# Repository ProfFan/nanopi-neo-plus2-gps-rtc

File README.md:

# NanoPi GPS/RTC HAT

GPS Tested, RTC NOT Tested!

Note that you need to compile `GPSD` and `Chrony` yourself as the version supplied with Armbian DOES NOT WORK!

# BOM

| Id | Designator | Package                                         | Quantity | Designation       |
|----|------------|-------------------------------------------------|----------|-------------------|
| 1  | U2         | SOIC-16W_7.5x10.3mm_P1.27mm                     | 1        | DS3231M           |
| 2  | SW1        | SW_SPST_EVQPE1 淘宝贴片轻触开关，长方形的6mm长  | 1        | SW_Push           |
| 3  | R4,R3,R2   | R_0805_2012Metric                               | 3        | NP                |
| 4  | C2         | C_0805_2012Metric                               | 1        | 1u                |
| 5  | J4         | PinSocket_1x08_P2.54mm_Vertical 1P8 母头        | 1        | Conn_01x08_Female |
| 6  | J3         | PinSocket_1x12_P2.54mm_Vertical 1P12 母头       | 1        | Conn_01x12_Female |
| 7  | R1         | R_0805_2012Metric                               | 1        | 10                |
| 8  | L1         | L_0805_2012Metric                               | 1        | 27n               |
| 9  | J2         | PinHeader_2x12_P2.54mm_Vertical 2P12 母头       | 1        | NanoPi_GPIO       |
| 10 | C1         | C_0805_2012Metric                               | 1        | 47p               |
| 11 | BT1        | BatteryHolder_Seiko_MS621F 贴片纽扣电池 3V      | 1        | Battery_Cell      |
| 12 | J1         | U.FL_Molex_MCRF_73412-0110_Vertical 淘宝 uFL 座 | 1        | Conn_Coaxial      |
| 13 | U1         | KH-1110 立创，可买 JS-U810 （兼容）             | 1        | KH-1110-UB8X      |

# LICENSE

CERN OHL version 1.2

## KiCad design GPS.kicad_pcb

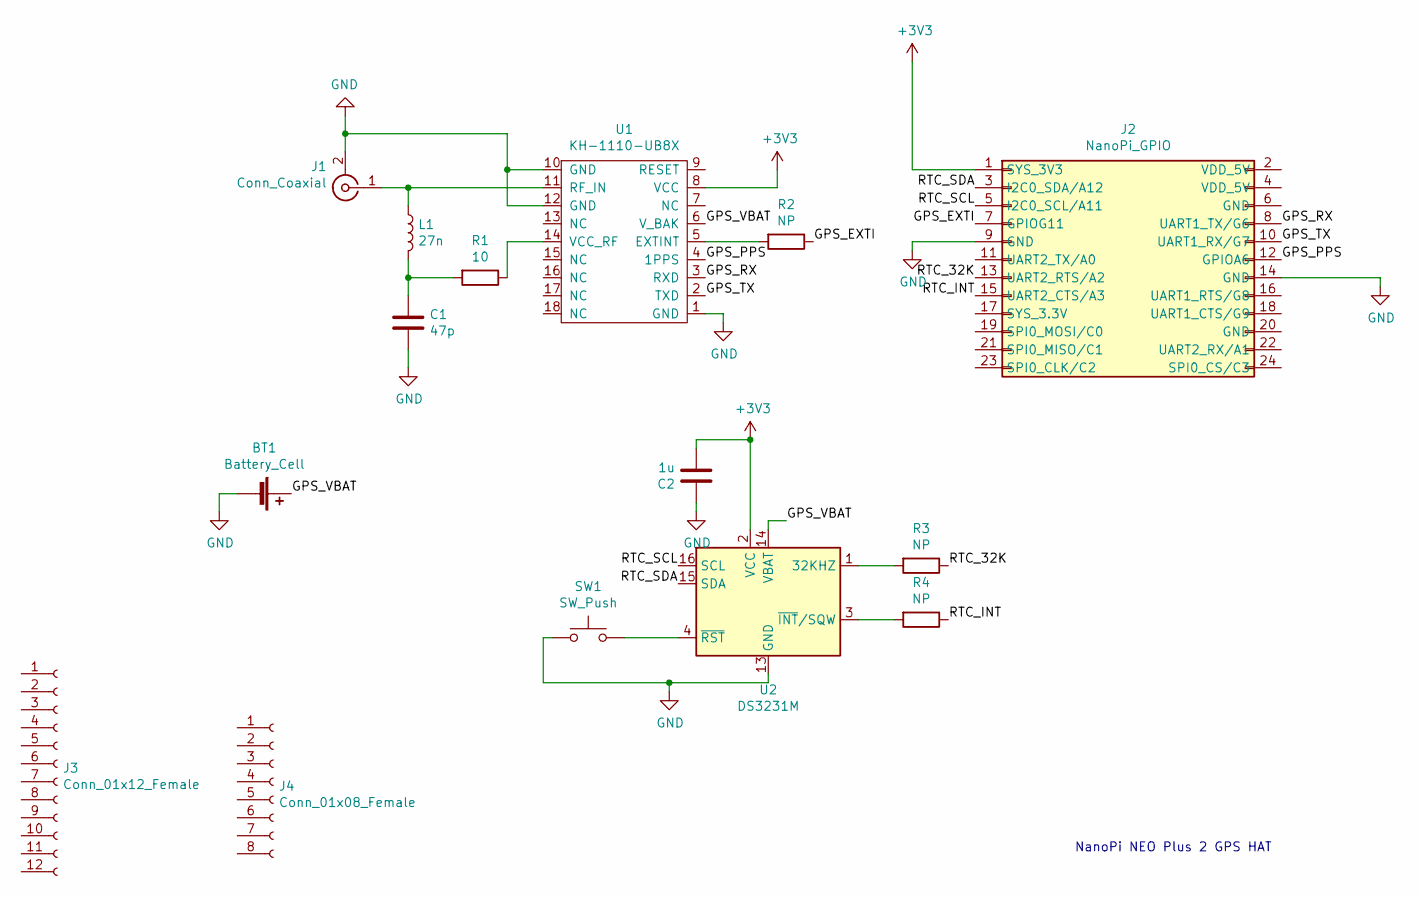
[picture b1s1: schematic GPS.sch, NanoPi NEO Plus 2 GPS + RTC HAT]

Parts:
BT1: Battery_Cell; BatteryHolder_Seiko_MS621F
C1: 47p; C_0805_2012Metric
C2: 1u; C_0805_2012Metric
J1: Conn_Coaxial; U.FL_Molex_MCRF_73412-0110_Vertical
J2: NanoPi_GPIO; PinHeader_2x12_P2.54mm_Vertical
J3: Conn_01x12_Female; PinSocket_1x12_P2.54mm_Vertical
J4: Conn_01x08_Female; PinSocket_1x08_P2.54mm_Vertical
L1: 27n; L_0805_2012Metric
R1: 10; R_0805_2012Metric
R2, R3, R4: NP; R_0805_2012Metric
SW1: SW_Push; SW_SPST_EVQPE1
U1: KH-1110-UB8X; KH-1110
U2: DS3231M; SOIC-16W_7.5x10.3mm_P1.27mm

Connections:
+3V3: C2.2, J2.1 (SYS_3V3), U1.8 (VCC), U2.2 (VCC)
/GPS_EXTI: J2.7 (GPIOG11), R2.1
/GPS_PPS: J2.12 (GPIOA6), U1.4 (1PPS)
/GPS_RX: J2.8 (UART1_TX/G6), U1.3 (RXD)
/GPS_TX: J2.10 (UART1_RX/G7), U1.2 (TXD)
/GPS_VBAT: BT1.1 (+), U1.6 (V_BAK), U2.14 (VBAT)
/RTC_32K: J2.13 (UART2_RTS/A2), R3.1
/RTC_INT: J2.15 (UART2_CTS/A3), R4.1
/RTC_SCL: J2.5 (I2C0_SCL/A11), U2.16 (SCL)
/RTC_SDA: J2.3 (I2C0_SDA/A12), U2.15 (SDA)
GND: BT1.2 (-), C1.2, C2.1, J1.2 (Ext), J2.9 (GND), J2.14 (GND), SW1.1, U1.1 (GND), U1.10 (GND), U1.12 (GND), U2.5 (GND), U2.6 (GND), U2.7 (GND), U2.8 (GND), U2.9 (GND), U2.10 (GND), U2.11 (GND), U2.12 (GND), U2.13 (GND)
unnamed: C1.1, L1.2, R1.2
unnamed: J1.1 (In), L1.1, U1.11 (RF_IN)
unnamed: R1.1, U1.14 (VCC_RF)
unnamed: R2.2, U1.5 (EXTINT)
unnamed: R3.2, U2.1 (32KHZ)
unnamed: R4.2, U2.3 (~INT~/SQW)
unnamed: SW1.2, U2.4 (~RST)

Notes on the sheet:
NanoPi NEO Plus 2 GPS HAT

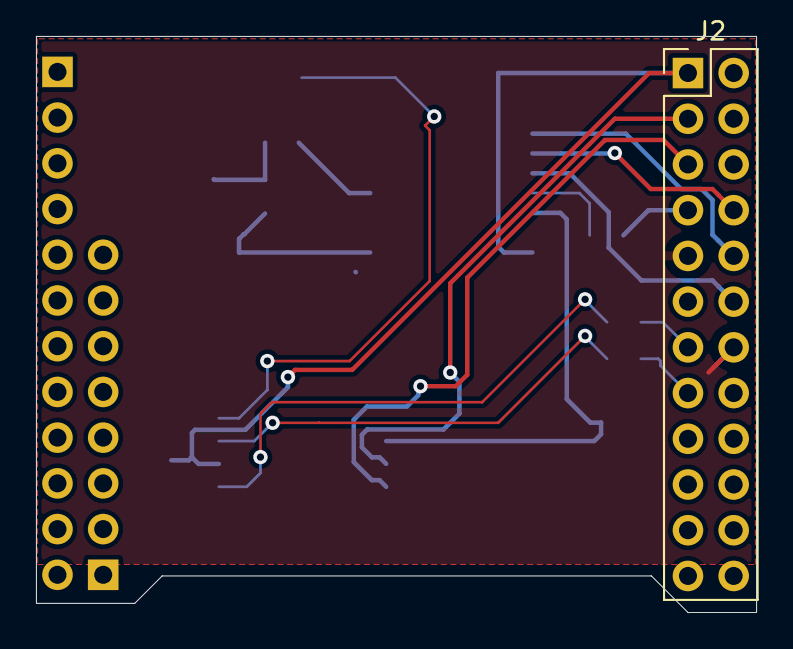
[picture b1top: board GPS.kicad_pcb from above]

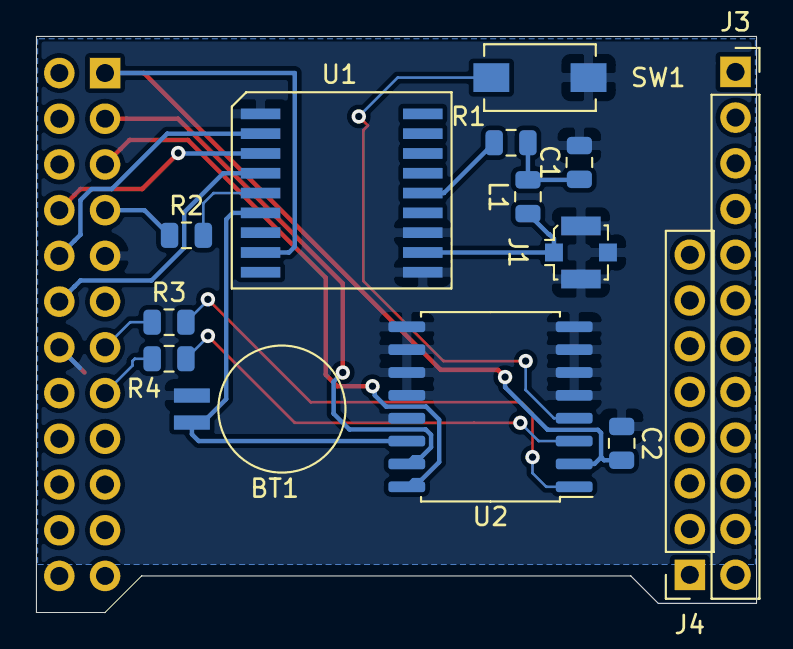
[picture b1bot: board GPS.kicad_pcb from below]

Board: 2 copper layers, 40.0 x 32.0 mm, 15 parts (14 on the bottom side), 18 nets.

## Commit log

2019-07-12 With RTC
2019-07-12 README
2019-07-12 Add BOM
2019-07-12 Add Chinese BOM
